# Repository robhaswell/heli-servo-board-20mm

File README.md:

# Helicopter servo bus board
This project is a PCB designed to facilitate wiring a helicopter servo bus to a drone flight controller.

Mounting pattern: 20x20mm.

This bus supports 3 servo outputs and so must be used for helicopters with a motor-driven tail connected to an ESC.

The connector footprints are for 1.25mm pitch connectors, such as Molex PicoBlade or JST 1.25.

**Please read the [assembly instructions](#assembly-instructions) before ordering or use**

## Instructions for ordering

First: Read the [assembly instructions](#assembly-instructions) and determine that this board is suitable for your setup.

You can order this PCB with a prototyping service.
Below are instructions for using [JLCPCB](https://jlcpcb.com):

1. Visit https://jlcpcb.com/.
2. Click "Order now' from the menu - do not use the quoting box.
3. Upload the file [gerber.zip](gerber.zip).
4. You may use the default options, but I suggest selecting a thickness of 0.8mm or 1.0mm. I also prefer the black PCBs.
5. Add to basket and check out. Take care to review the shipping options. FedEx is good if you would like this sooner, but there is usually a very cheap option depending on your location.

## Assembly instructions

To assemble you will need:

1. PicoBlade or JST 1.25 connectors to match your servo plugs.
2. JST-XH 2-way horizontal connector `S2B-XH-A(LF)(SN)`  
or  
JST-XH vertical or other 2.54mm connector.  
or  
JST-PH or other 2.00mm connector.

**Pay very close attention to plug wiring, pins and polarities!!!**

There are no standard servo plug pinouts.
Test everything with a multimeter before soldering, and again before powering on.

1. Make sure that your intended servos have the control wire as pin 1 or 3.
2. Solder your servo input connector, or use the solder pads directly. These are the control lines from your PWM servo outputs on your FC. If using solder pads you can solder directly to the wire pads, connector pads, or both. Use silicone glue to secure the wire.
3. Solder your servo connectors so that the control wire is the topmost pin, the row labelled "1".
4. Check the position of your servo positive and negative wires. They should line up with "V" (positive) and "G" (negative). If they do not (e.g. Blade servos) then you will need to install the power connector backwards.
5. Check the pins of your power connector and verify correct pins with a multimeter, then solder.
6. Test all connections a final time.

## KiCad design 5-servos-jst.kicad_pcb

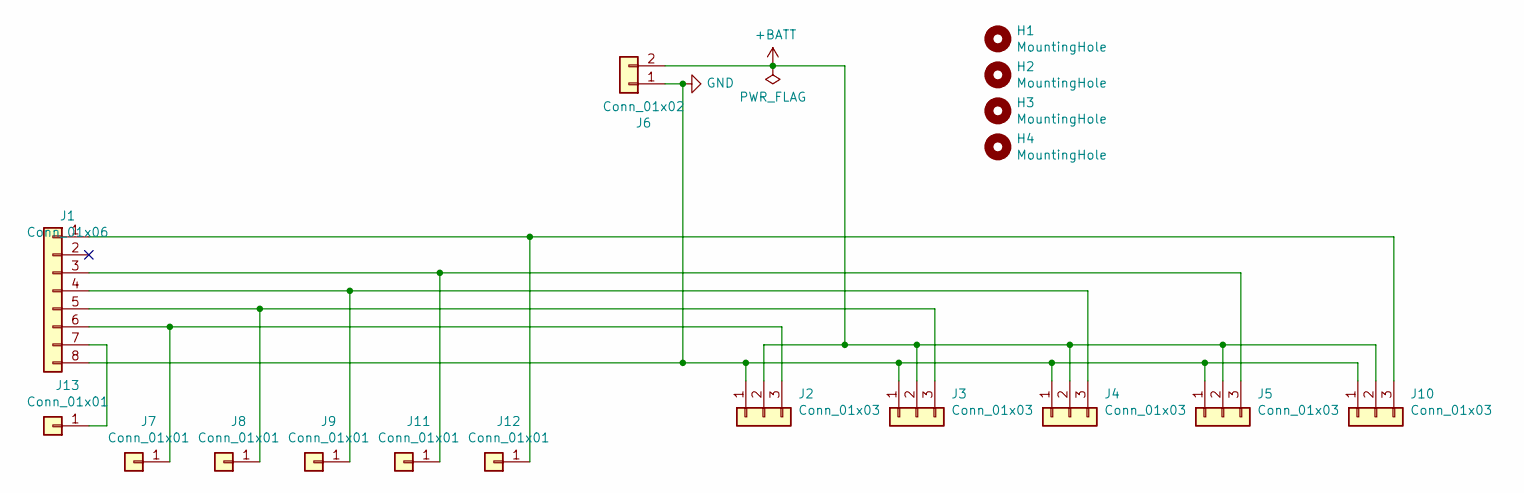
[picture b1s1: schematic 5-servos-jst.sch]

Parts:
H1, H2, H3, H4: MountingHole; MountingHole_3.2mm_M3
J1: Conn_01x06; JST_SHL_SM08B-SHLS-TF_1x08-1MP_P1.00mm_Horizontal
J2, J3: Conn_01x03; PinHeader_1x03_P2.54mm_Vertical
J4, J5, J10: Conn_01x03; Molex_PicoBlade_53047-0310_1x03_P1.25mm_Vertical
J6: Conn_01x02; JST_XH_S2B-XH-A_1x02_P2.50mm_Horizontal
J7, J8, J9, J11, J12, J13: Conn_01x01; SolderWirePad_1x01_SMD_1x2mm

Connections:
+BATT: J2.2, J3.2, J4.2, J5.2, J6.2, J10.2
GND: J1.8, J2.1, J3.1, J4.1, J5.1, J6.1, J10.1
unnamed: J1.1, J10.3, J12.1
unnamed: J1.3, J5.3, J11.1
unnamed: J1.4, J4.3, J9.1
unnamed: J1.5, J3.3, J8.1
unnamed: J1.6, J2.3, J7.1
unnamed: J1.7, J13.1

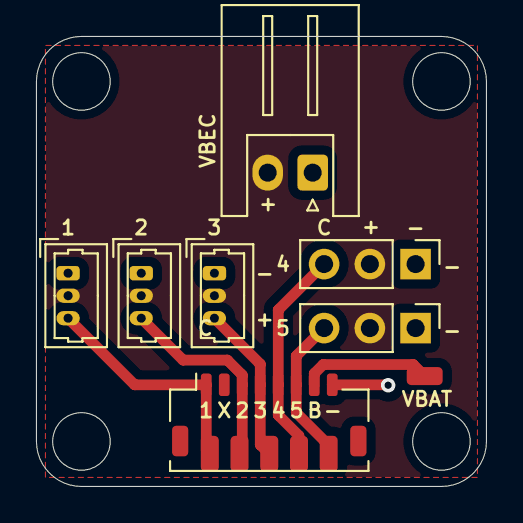
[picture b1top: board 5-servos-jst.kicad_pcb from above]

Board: 2 copper layers, 25.0 x 25.0 mm, 17 parts (0 on the bottom side), 8 nets.

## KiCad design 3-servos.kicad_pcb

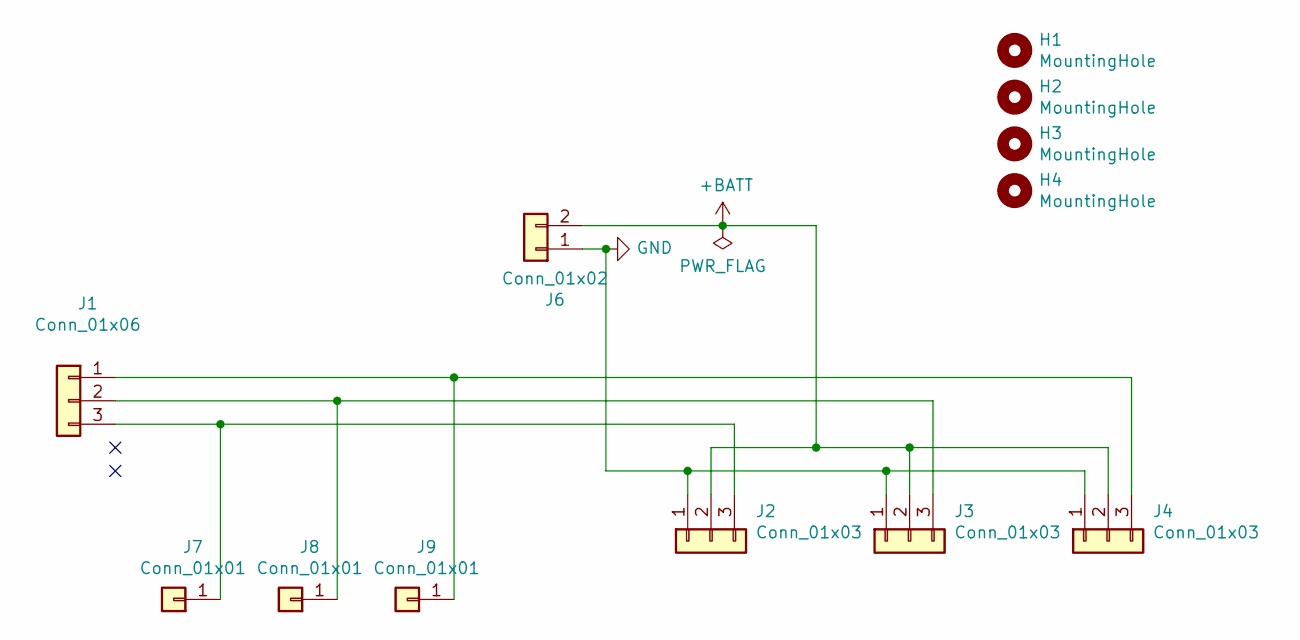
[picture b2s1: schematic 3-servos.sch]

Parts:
H1, H2, H3, H4: MountingHole; MountingHole_2.2mm_M2
J1: Conn_01x06; Molex_PicoBlade_53047-0310_1x03_P1.25mm_Vertical
J2, J3, J4: Conn_01x03; Molex_PicoBlade_53047-0310_1x03_P1.25mm_Vertical
J6: Conn_01x02; JST_XH_S2B-XH-A_1x02_P2.50mm_Horizontal
J7, J8, J9: Conn_01x01; SolderWirePad_1x01_SMD_1x2mm

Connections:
+BATT: J2.2, J3.2, J4.2, J6.2
GND: J2.1, J3.1, J4.1, J6.1
unnamed: J1.1, J4.3, J9.1
unnamed: J1.2, J3.3, J8.1
unnamed: J1.3, J2.3, J7.1

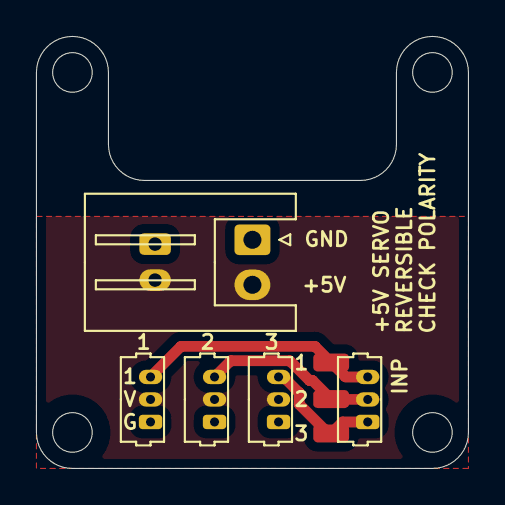
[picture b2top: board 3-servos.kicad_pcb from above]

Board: 2 copper layers, 24.0 x 24.0 mm, 12 parts (0 on the bottom side), 5 nets.

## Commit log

2021-08-13 Create 5-servo version.
2021-10-08 Add 5 servo board with JST and M3 holes.
